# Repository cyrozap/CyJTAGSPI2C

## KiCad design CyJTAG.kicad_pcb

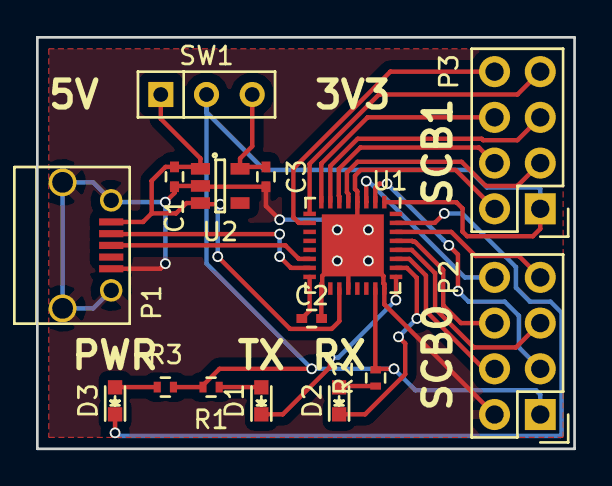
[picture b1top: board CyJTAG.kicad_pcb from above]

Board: 2 copper layers, 29.8 x 22.9 mm, 15 parts (0 on the bottom side), 25 nets.

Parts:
C1: 0.1uF; C_0402
C2, C3: 1.0uF; C_0402
D1, D2, D3: LED; LED-0603
P1: USB_B; USB_Micro-B
P2, P3: CONN_02X04; Pin_Header_Straight_2x04
R1, R2, R3: 1k; R_0402
SW1: Switch_SPDT; SW_Micro_SPST
U1: CY7C65215; QFN-32-1EP_5x5mm_Pitch0.5mm
U2: TLV70233DBV; SOT-23-5

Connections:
+3V3: C3.1, SW1.3, U2.5
+5V: C1.1, P1.1, SW1.1, U1.19, U2.1, U2.3
//POWER: D3.1, U1.31
//RXLED: D2.1, U1.26
//TXLED: D1.1, U1.25
/SCB0_0: P2.3, U1.2
/SCB0_1: P2.4, U1.27
/SCB0_2: P2.5, U1.28
/SCB0_3: P2.6, U1.29
/SCB0_4: P2.7, U1.30
/SCB0_5: P2.8, U1.3
/SCB1_0: P3.3, U1.5
/SCB1_1: P3.4, U1.6
/SCB1_2: P3.5, U1.7
/SCB1_3: P3.6, U1.8
/SCB1_4: P3.7, U1.9
/SCB1_5: P3.8, U1.10
/USBDM: P1.2, U1.15
/USBDP: P1.3, U1.14
GND: C1.2, C2.2, C3.2, P1.5, P1.6, P2.2, P3.2, U1.4, U1.17, U1.20, U1.24, U1.33, U2.2
unnamed: C2.1, U1.16
unnamed: D1.2, R1.1
unnamed: D2.2, R2.1
unnamed: D3.2, R3.1
VDD: P2.1, P3.1, R1.2, R2.2, R3.2, SW1.2, U1.1, U1.23

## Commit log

2015-08-20 Fixed polyfills
2015-08-20 Set OSHPark plotting parameters
2015-08-21 Updated schematic and layout
    1. Added missing reset pull-up in layout
    2. Made USB port mounting holes circular (for OSHPark)
    3. Removed the default GPIO functions from the IC symbol
    4. General layout cleanup
2015-08-21 Set the gerber output directory
2015-08-22 Updated board to switch between 5V and 3.3V
2015-09-08 Removed unnecessary resistor and corrected VBUS source
2015-09-08 Moved the voltage switch, some of the silkscreen text, and optimized some paths
2015-09-23 Don't plot references
2015-10-25 Added gitignore
2015-10-25 Swap USB DM/DP labels
2015-10-25 Simplified board by removing GPIO header and adding power, Rx, and Tx LEDs
2016-02-21 Changed license to CERN OHL v1.2

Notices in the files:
CyJTAG.kicad_pcb:
©2015 Forest Crossman
